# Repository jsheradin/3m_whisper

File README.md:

# 3m_whisper
USB conversion for a 3M Whisper Writer Keyboard

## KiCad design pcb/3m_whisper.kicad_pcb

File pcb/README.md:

You can upload the gerber zip to pretty much any PCB fab-house no problem.

Libraries are not mine, I just chopped up a couple of the footprints to suit my needs.

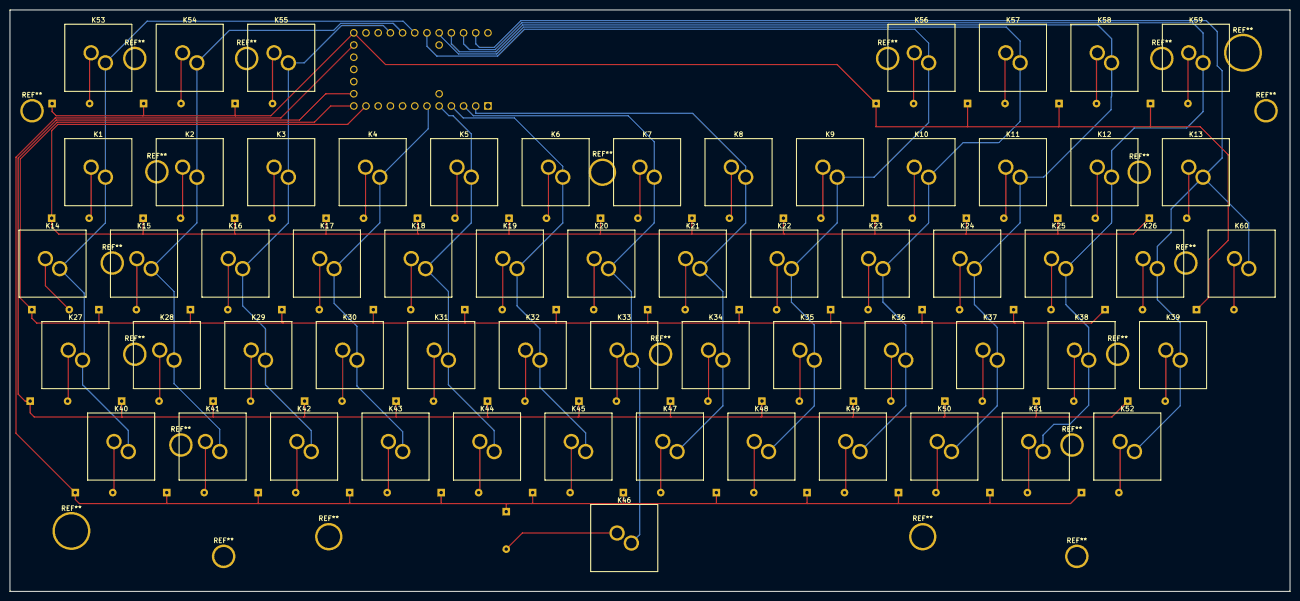
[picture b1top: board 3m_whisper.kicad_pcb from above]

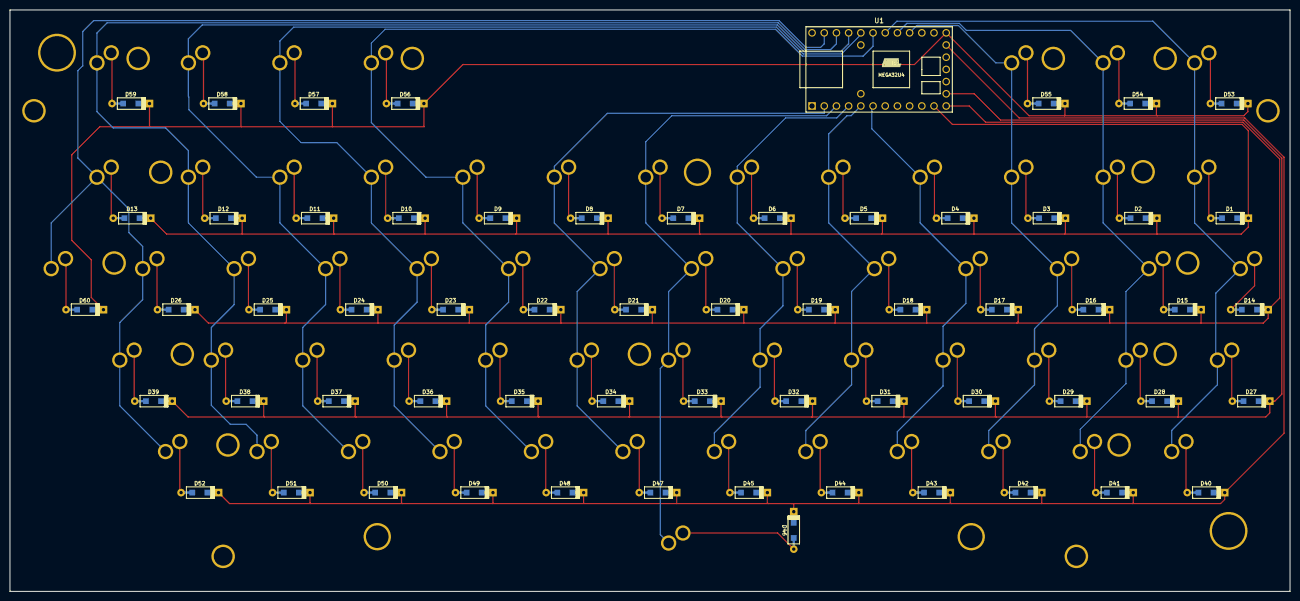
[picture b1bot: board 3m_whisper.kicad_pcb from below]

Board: 2 copper layers, 266.6 x 121.1 mm, 121 parts (61 on the bottom side), 78 nets.

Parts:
D1, D2, D3, D4, D5, D6, D7, D8, D9, D10, D11, D12, D13, D14, D15, D16, D17, D18, D19, D20, D21, D22, D23, D24, D25, D26, D27, D28, D29, D30, D31, D32, D33, D34, D35, D36, D37, D38, D39, D40, D41, D42, D43, D44, D45, D46, D47, D48, D49, D50, D51, D52, D53, D54, D55, D56, D57, D58, D59, D60: D; D_SOD123_axial
K1, K2, K3, K4, K5, K6, K7, K8, K9, K10, K11, K12, K13, K14, K15, K16, K17, K18, K19, K20, K21, K22, K23, K24, K25, K26, K27, K28, K29, K30, K31, K32, K33, K34, K35, K36, K37, K38, K39, K40, K41, K42, K43, K44, K45, K46, K47, K48, K49, K50, K51, K52, K53, K54, K55, K56, K57, K58, K59, K60: KEYSW; Stackpole
U1: TEENSY2.0; Teensy2.0

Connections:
/col0: K1.1, K14.1, K27.1, K40.1, K53.1, U1.23
/col1: K2.1, K15.1, K28.1, K41.1, K54.1, U1.22
/col2: K3.1, K16.1, K29.1, K42.1, K55.1, U1.21
/col3: K4.1, K17.1, K30.1, K43.1, U1.6
/col4: K5.1, K18.1, K31.1, K44.1, U1.5
/col5: K6.1, K19.1, K32.1, K45.1, U1.4
/col6: K7.1, K20.1, K33.1, K46.1, U1.3
/col7: K8.1, K21.1, K34.1, K47.1, U1.2
/col8: K9.1, K22.1, K35.1, K48.1, K56.1, U1.24
/col9: K10.1, K23.1, K36.1, K49.1, K57.1, U1.25
/col10: K11.1, K24.1, K37.1, K50.1, K58.1, U1.26
/col11: K12.1, K25.1, K38.1, K51.1, K59.1, U1.27
/col12: K13.1, K26.1, K39.1, K52.1, K60.1, U1.28
/row0: D1.1, D2.1, D3.1, D4.1, D5.1, D6.1, D7.1, D8.1, D9.1, D10.1, D11.1, D12.1, D13.1, U1.11
/row1: D14.1, D15.1, D16.1, D17.1, D18.1, D19.1, D20.1, D21.1, D22.1, D23.1, D24.1, D25.1, D26.1, U1.12
/row2: D27.1, D28.1, D29.1, D30.1, D31.1, D32.1, D33.1, D34.1, D35.1, D36.1, D37.1, D38.1, D39.1, U1.13
/row3: D40.1, D41.1, D42.1, D43.1, D44.1, D45.1, D46.1, D47.1, D48.1, D49.1, D50.1, D51.1, D52.1, U1.17
/row4: D53.1, D54.1, D55.1, D56.1, D57.1, D58.1, D59.1, D60.1, U1.18
unnamed: D1.2, K1.2
unnamed: D2.2, K2.2
unnamed: D3.2, K3.2
unnamed: D4.2, K4.2
unnamed: D5.2, K5.2
unnamed: D6.2, K6.2
unnamed: D7.2, K7.2
unnamed: D8.2, K8.2
unnamed: D9.2, K9.2
unnamed: D10.2, K10.2
unnamed: D11.2, K11.2
unnamed: D12.2, K12.2
unnamed: D13.2, K13.2
unnamed: D14.2, K14.2
unnamed: D15.2, K15.2
unnamed: D16.2, K16.2
unnamed: D17.2, K17.2
unnamed: D18.2, K18.2
unnamed: D19.2, K19.2
unnamed: D20.2, K20.2
unnamed: D21.2, K21.2
unnamed: D22.2, K22.2
unnamed: D23.2, K23.2
unnamed: D24.2, K24.2
unnamed: D25.2, K25.2
unnamed: D26.2, K26.2
unnamed: D27.2, K27.2
unnamed: D28.2, K28.2
unnamed: D29.2, K29.2
unnamed: D30.2, K30.2
unnamed: D31.2, K31.2
unnamed: D32.2, K32.2
unnamed: D33.2, K33.2
unnamed: D34.2, K34.2
unnamed: D35.2, K35.2
unnamed: D36.2, K36.2
unnamed: D37.2, K37.2
unnamed: D38.2, K38.2
unnamed: D39.2, K39.2
unnamed: D40.2, K40.2
unnamed: D41.2, K41.2
unnamed: D42.2, K42.2
unnamed: D43.2, K43.2
unnamed: D44.2, K44.2
unnamed: D45.2, K45.2
unnamed: D46.2, K46.2
unnamed: D47.2, K47.2
unnamed: D48.2, K48.2
unnamed: D49.2, K49.2
unnamed: D50.2, K50.2
unnamed: D51.2, K51.2
unnamed: D52.2, K52.2
unnamed: D53.2, K53.2
unnamed: D54.2, K54.2
unnamed: D55.2, K55.2
unnamed: D56.2, K56.2
unnamed: D57.2, K57.2
unnamed: D58.2, K58.2
unnamed: D59.2, K59.2
unnamed: D60.2, K60.2

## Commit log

2021-03-13 send pics
